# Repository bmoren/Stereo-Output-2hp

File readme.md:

## Passive Stereo output in 2hp (a companion for [nearness](https://github.com/sarnesjo/nearness))

[more info here...](https://llllllll.co/t/2hp-passive-stereo-output-a-companion-for-nearness/14189)

Most of the stereo outs on the market are quite large and with a nearness you can quickly create a large stereo field. Having the extra pan knobs on most stereo outs tends to be irrelevant when using nearness (well, less relevant). The new ALM output looks good, but I wanted to put together a super-duper easy DIY kit. This thing is totally passive & so simple, there aren’t even any resistors! here is the BOM:

+ a PCB
+ a panel
+ 2 mono thonkiconn jacks
+ 2 9mm tall trimmer pots
+ 1 stereo thonkiconn jack

The only thing you need to know about assembly besides looking at the picture for parts placement is to solder the jacks first, then the pots.

 I suggest you do the jacks while screwed into the panel. Then take the panel off and insert and bend the pots. When soldering the pots, put the panel back on again to make sure everything is lined up properly!

 The stabilizing legs of the pots are bent around the outside of the PCB and soldered on the back side to rectangular pads. Make sure that the jacks remain vertical when doing this!

---
[CC BY-SA 4.0](https://creativecommons.org/licenses/by-sa/4.0/).   
Build and use at your own risk! I am not responsible for any damage to self or otherwise that arises from using this project!

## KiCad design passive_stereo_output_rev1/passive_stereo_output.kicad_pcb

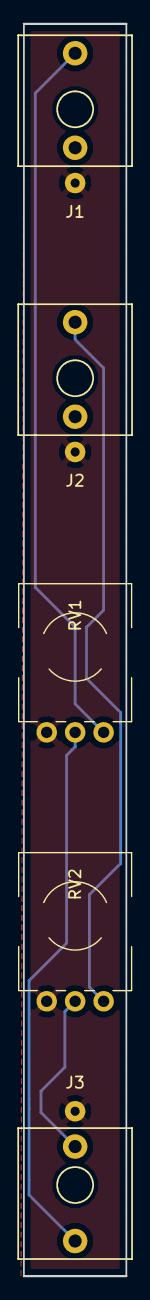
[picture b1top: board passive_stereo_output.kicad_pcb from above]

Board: 2 copper layers, 9.0 x 110.0 mm, 5 parts (0 on the bottom side), 5 nets.

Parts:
J1, J2: thonkiconn; Thonkiconn_small_holes
J3: Audio-Jack-3; Thonkiconn_small_holes
RV1, RV2: POT; potentiometer_2hp_back_pad_mount

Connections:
GNDREF: J1.1, J2.1, J3.1, RV1.1, RV2.1
unnamed: J1.3, RV1.3
unnamed: J2.3, RV2.3
unnamed: J3.2, RV2.2
unnamed: J3.3, RV1.2

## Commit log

2018-06-06 init
2018-06-06 clean
2018-06-06 remove dsstore
2018-06-06 add lic
2018-06-06 assembly instructions

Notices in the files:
passive_stereo_output_rev1/passive_stereo_output.kicad_pcb:
CC BY SA NC
